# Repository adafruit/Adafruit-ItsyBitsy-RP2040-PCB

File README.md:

## Adafruit ItsyBitsy RP2040 PCB

<a href="http://www.adafruit.com/products/4888"><br/>
Click here to purchase one from the Adafruit shop</a>

PCB files for the Adafruit ItsyBitsy RP2040.

Format is EagleCAD schematic and board layout
* https://www.adafruit.com/product/4888

### Description

A new chip means a new ItsyBitsy, and the Raspberry Pi RP2040 is no exception. When we saw this chip we thought "this chip is going to be awesome when we give it the ItsyBitsy teensy-weensy Treatment" and so we did! This Itsy' features the RP2040, and all niceties you know and love about the ItsyBitsy family.

What's smaller than a Feather but larger than a Trinket? It's an Adafruit ItsyBitsy RP2040 featuring the Raspberry Pi RP2040! Small, powerful, with a ultra fast dual Cortex M0+ processor running at 125 MHz - this microcontroller board is perfect when you want something very compact, with lots of horsepower and a bunch of pins. This Itsy has sports car speed, but SUV roominess with 8 MB of FLASH and 264KB of SRAM.

ItsyBitsy RP2040 is only 1.4" long by 0.7" wide, but has 6 power pins, 23 digital GPIO pins (4 of which can be analog in and 16 x PWM out). It's the same chip as the Feather RP2040 and Raspberry Pi Pico but really really small. So it's great once you've finished up a prototype, and want to make the project much smaller. It even comes with 8 MB of SPI Flash built in, for data logging, file storage, or CircuitPython/MicroPython code

* Same size and form-factor as the rest of the ItsyBitsy family and nearly-identical pinout
* Measures 1.4" x 0.7" x 0.2" (36mm x 18mm x 4mm) without headers soldered in
* RP2040 32-bit Cortex M0+ dual core running at ~125 MHz @ 3.3V logic and power
* 264 KB RAM
* 8 MB SPI FLASH chip for storing files and CircuitPython/MicroPython code storage. No EEPROM
* Tons of GPIO! 23 x GPIO pins with following capabilities:
  * Four 12 bit ADCs (one more than Pico)
  * Two I2C, Two SPI and two UART peripherals, we label one for the 'main' interface in standard ItsyBitsy locations
  * 16 x PWM outputs - for servos, LEDs, etc
  * The 10 digital 'non-ADC/non-peripheral' GPIO are consecutive for maximum PIO compatibility
* Pin #13 red LED for general purpose blinking
* RGB NeoPixel with power pin on GPIO so you can depower it for low power usages.
* Both Reset button and Bootloader select button for quick restarts (no unplugging-replugging to relaunch code)
* 3.3V regulator with 500mA peak current output
* 3.3V Power/enable pin
* Power with either USB or external output (such as a battery) - it'll automatically switch over
* Broken-out SWD pins for debug access
* 12 MHz crystal for perfect timing.
* Special Vhigh output pin gives you the higher voltage from VBAT or VUSB, for driving NeoPixels, servos, and other 5V-logic devices. Digital 5 level-shifted output for high-voltage logic level output.
* USB Micro B connector lets you access built-in ROM USB bootloader and serial port debugging

Inside the RP2040 is a 'permanent ROM' USB UF2 bootloader. What that means is when you want to program new firmware, you can hold down the BOOTSEL button while plugging it into USB (or pulling down the RUN/Reset pin to ground) and it will appear as a USB disk drive you can drag the firmware onto. Folks who have been using Adafruit products will find this very familiar - we use the technique on all our native-USB boards. Just note you don't double-click reset, instead hold down BOOTSEL during boot to enter the bootloader!

The RP2040 is a powerful chip, which has the clock speed of our M4 (SAMD51), and two cores that are equivalent to our M0 (SAMD21). Since it is an M0 chip, it does not have a floating point unit or DSP hardware support - so if you're doing something with heavy floating point math, it will be done in software and thus not as fast as an M4. For many other computational tasks, you'll get close-to-M4 speeds!

For peripherals, there are two I2C controllers, two SPI controllers, and two UARTs that are multiplexed across the GPIO - check the pinout for what pins can be set to which. There are 16 PWM channels, each pin has a channel it can be set to (ditto on the pinout).

You'll note there's no I2S peripheral, or SDIO, or camera, what's up with that? Well instead of having specific hardware support for serial-data-like peripherals like these, the RP2040 comes with the PIO state machine system which is a unique and powerful way to create custom hardware logic and data processing blocks that run on their own without taking up a CPU. For example, NeoPixels - often we bitbang the timing-specific protocol for these LEDs. For the RP2040, we instead use PIO object that reads in the data buffer and clocks out the right bitstream with perfect accuracy. Same with I2S audio in or out, LED matrix displays, 8-bit or SPI based TFTs, even VGA! In MicroPython and CircuitPython you can create PIO control commands to script the peripheral and load it in at runtime. There are 2 PIO peripherals with 4 state machines each.

At the time of launch, there is no Arduino core support for this board. There is great C/C++ support, an official MicroPython port, and a CircuitPython port! We of course recommend CircuitPython because we think it's the easiest way to get started and it has support with most of our drivers, displays, sensors, and more, supported out of the box so you can follow along with our CircuitPython projects and tutorials.

This Itsy comes with loose 0.1" headers you can solder in for breadboard use!

While the RP2040 has lots of onboard RAM (264KB), it does not have built-in FLASH memory. Instead, that is provided by the external QSPI flash chip. On this board there is 8 MB, which is shared between the program it's running and any file storage used by MicroPython or CircuitPython. When using C/C++ you get the whole flash memory, if using Python you will have about 7 MB remaining for code, files, images, fonts, etc.

### License

Adafruit invests time and resources providing this open source design, please support Adafruit and open-source hardware by purchasing products from [Adafruit](https://www.adafruit.com)!

Designed by Limor Fried/Ladyada for Adafruit Industries.

Creative Commons Attribution/Share-Alike, all text above must be included in any redistribution.
See license.txt for additional details.

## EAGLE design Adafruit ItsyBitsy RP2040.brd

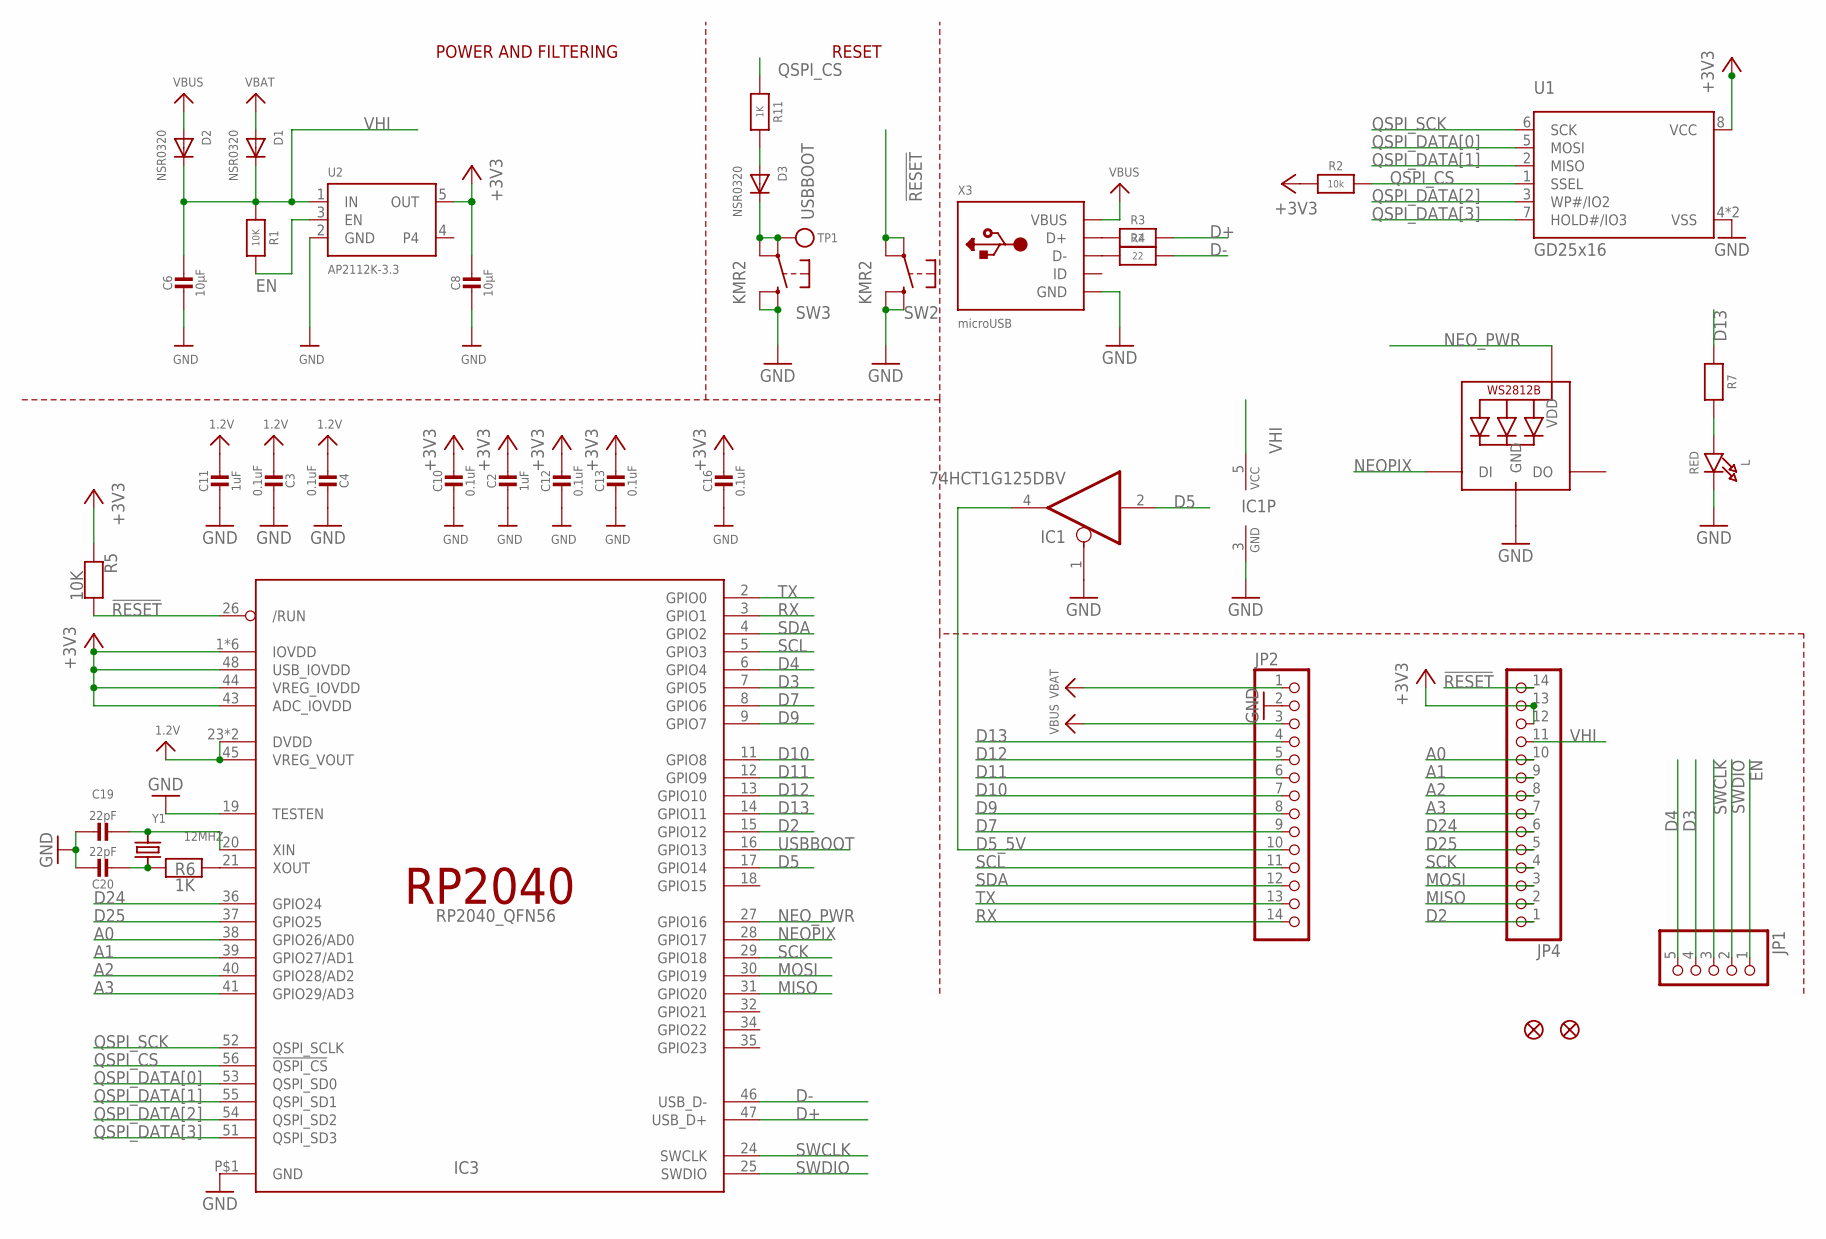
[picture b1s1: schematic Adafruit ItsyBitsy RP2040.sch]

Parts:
C2, C11: 1uF; _0603MP
C3, C4, C10, C12, C13, C16: 0.1uF; _0402NO
C6, C8: 10µF; 0805-NO
C19, C20: 22pF; _0402NO
D1, D2, D3: NSR0320; SOD-323F
IC1: 74HCT1G125DBV; SC70-5
IC3: RP2040_QFN56; QFN56_7MM_REDUCEDEPAD
JP1: HEADER-1X570MIL; 1X05_ROUND_70
JP2, JP4: HEADER-1X14; 1X14_ROUND70
L: RED; CHIPLED_0603_NOOUTLINE
LED1: WS2812B_SK6805_1515; SK6805_1515
R1, R5: 10K; _0402NO
R2: 10k; _0402NO
R3, R4: 22; _0402NO
R6, R7, R11: 1K; _0402NO
SW2, SW3: KMR2; BTN_KMR2_4.6X2.8
TP1: TESTPOINTROUND1.5MMNO; TESTPOINT_ROUND_1.5MM_NO
U1: GD25x16; USON8_4X4
U2: AP2112K-3.3; SOT23-5
U$34, U$35: FIDUCIAL_1MM
X3: microUSB; 4UCONN_20329_NARROW
Y1: 12MHZ; CRYSTAL_2.5X2

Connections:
1.2V: C3.2, C4.2, C11.1, IC3.23 (DVDD), IC3.45 (VREG_VOUT), IC3.50 (DVDD)
!RESET: IC3.26 (/RUN), JP4.14, R5.2, SW2.A, SW2.A' (P1)
+3V3: C2.1, C8.1, C10.1, C12.1, C13.1, C16.1, IC3.1 (IOVDD), IC3.10 (IOVDD), IC3.22 (IOVDD), IC3.33 (IOVDD), IC3.42 (IOVDD), IC3.43 (ADC_IOVDD), IC3.44 (VREG_IOVDD), IC3.48 (USB_IOVDD), IC3.49 (IOVDD), JP4.12, JP4.13, R2.1, R5.1, U1.8 (VCC), U2.5 (OUT)
A0: IC3.38 (GPIO26/AD0), JP4.10
A1: IC3.39 (GPIO27/AD1), JP4.9
A2: IC3.40 (GPIO28/AD2), JP4.8
A3: IC3.41 (GPIO29/AD3), JP4.7
D2: IC3.15 (GPIO12), JP4.1
D3: IC3.7 (GPIO5), JP1.4
D4: IC3.6 (GPIO4), JP1.5
D5: IC1.2 (I), IC3.17 (GPIO14)
D5_5V: IC1.4 (O), JP2.10
D7: IC3.8 (GPIO6), JP2.9
D9: IC3.9 (GPIO7), JP2.8
D10: IC3.11 (GPIO8), JP2.7
D11: IC3.12 (GPIO9), JP2.6
D12: IC3.13 (GPIO10), JP2.5
D13: IC3.14 (GPIO11), JP2.4, R7.1
D24: IC3.36 (GPIO24), JP4.6
D25: IC3.37 (GPIO25), JP4.5
D+: IC3.47 (USB_D+), R3.2
D-: IC3.46 (USB_D-), R4.2
EN: JP1.1, R1.2, U2.3 (EN)
GND: C2.2, C3.1, C4.1, C6.2, C8.2, C10.2, C11.2, C12.2, C13.2, C16.2, C19.1, C20.1, IC1.1 (OE), IC1.3 (GND), IC3.19 (TESTEN), IC3.P$1 (GND), JP2.2, L.C, LED1.4 (GND), SW2.B (S), SW2.B' (S1), SW3.B (S), SW3.B' (S1), U1.4 (VSS), U1.PAD (VSS), U2.2 (GND), X3.BASE@1 (GND), X3.BASE@2 (GND), X3.GND, X3.SPRT@1 (GND), X3.SPRT@2 (GND), X3.SPRT@3 (GND), X3.SPRT@4 (GND)
MISO: IC3.31 (GPIO20), JP4.2
MOSI: IC3.30 (GPIO19), JP4.3
unnamed: R3.1, X3.D+
unnamed: L.A, R7.2
unnamed: R4.1, X3.D-
unnamed: D3.A, R11.2
unnamed: C19.2, IC3.20 (XIN), Y1.3 (2)
unnamed: C20.2, R6.1, Y1.1
unnamed: IC3.21 (XOUT), R6.2
NEOPIX: IC3.28 (GPIO17), LED1.1 (DI)
NEO_PWR: IC3.27 (GPIO16), LED1.2 (VDD)
QSPI_CS: IC3.56 (!QSPI_CS), R2.2, R11.1, U1.1 (SSEL)
QSPI_DATA[0]: IC3.53 (QSPI_SD0), U1.5 (MOSI)
QSPI_DATA[1]: IC3.55 (QSPI_SD1), U1.2 (MISO)
QSPI_DATA[2]: IC3.54 (QSPI_SD2), U1.3 (WP#/IO2)
QSPI_DATA[3]: IC3.51 (QSPI_SD3), U1.7 (HOLD#/IO3)
QSPI_SCK: IC3.52 (QSPI_SCLK), U1.6 (SCK)
RX: IC3.3 (GPIO1), JP2.14
SCK: IC3.29 (GPIO18), JP4.4
SCL: IC3.5 (GPIO3), JP2.11
SDA: IC3.4 (GPIO2), JP2.12
SWCLK: IC3.24 (SWCLK), JP1.3
SWDIO: IC3.25 (SWDIO), JP1.2
TX: IC3.2 (GPIO0), JP2.13
USBBOOT: D3.C, IC3.16 (GPIO13), SW3.A, SW3.A' (P1), TP1.P$1
VBAT: D1.A, JP2.1
VBUS: D2.A, JP2.3, X3.VBUS
VHI: C6.1, D1.C, D2.C, IC1.5 (VCC), JP4.11, R1.1, U2.1 (IN)

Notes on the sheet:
POWER AND FILTERING
RESET

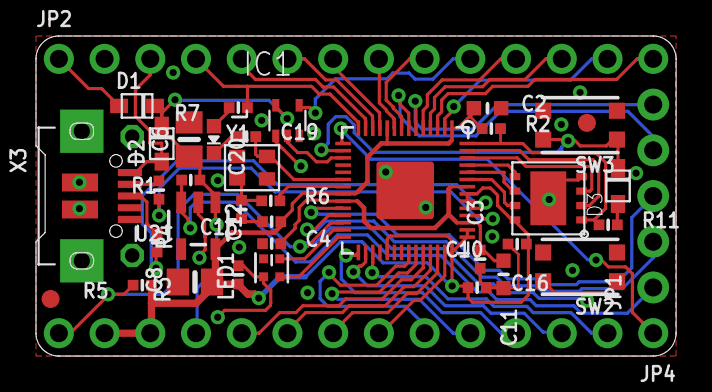
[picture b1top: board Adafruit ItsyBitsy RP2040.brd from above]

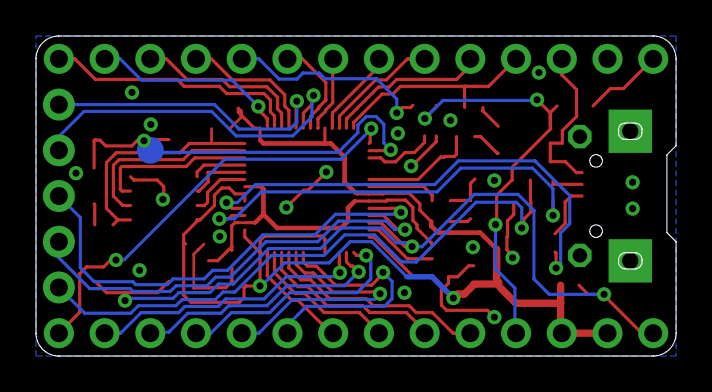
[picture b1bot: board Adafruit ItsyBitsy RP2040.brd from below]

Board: 2 copper layers, 35.6 x 17.8 mm, 41 parts (2 on the bottom side), 52 nets.

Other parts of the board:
U$4: ITSY2040_TOP
U$5: ITSY2040_BOT

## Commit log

2021-04-20 Adding board files.
2021-05-07 Adding pinout image file.
2021-12-10 Add PrettyPins PDF.

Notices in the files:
parts and their libraries:
microbuilder: This work is placed in the public domain, and may be freely used for commercial and non-commercial work with the following conditions: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
